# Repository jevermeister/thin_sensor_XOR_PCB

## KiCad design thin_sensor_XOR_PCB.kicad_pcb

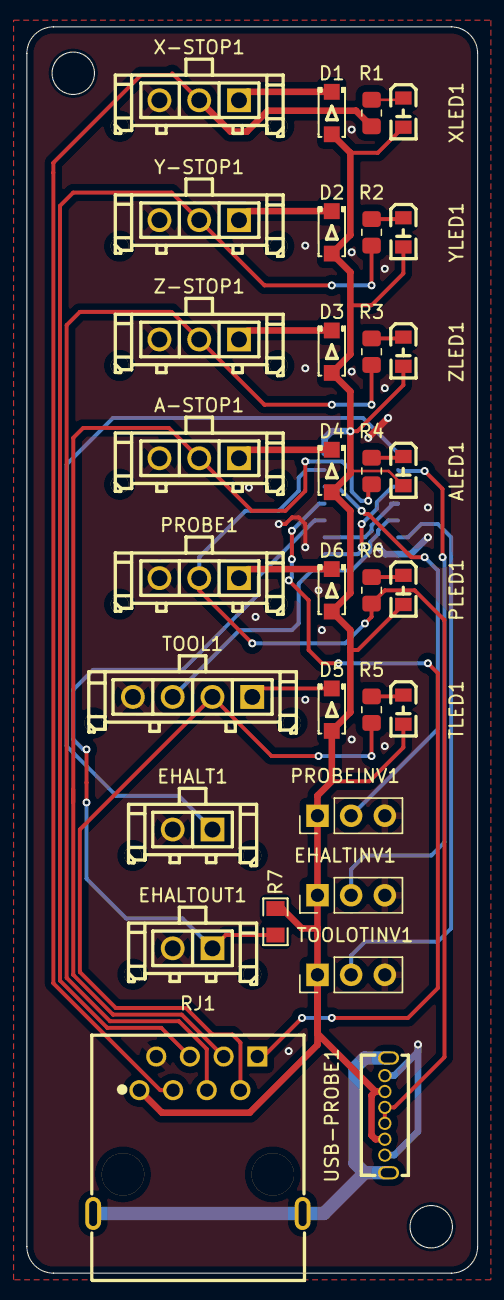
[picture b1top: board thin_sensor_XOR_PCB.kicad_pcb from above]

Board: 2 copper layers, 34.0 x 94.0 mm, 33 parts (1 on the bottom side), 30 nets.

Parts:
A-STOP1: Molex Microfit 3.0 43650-0315; CONN-TH_436500315
ALED1: LED0805-RD_RED
D1, D2, D3, D4, D5, D6: DSS14; SOD-123FL_L2.8-W1.8-LS3.7-RD
EHALT1: Molex Microfit 3.0 436500215; CONN-TH_436500215
EHALTINV1: Header-Male-2.54_1x3; PinHeader_1x03_P2.54mm_Vertical
EHALTOUT1: Molex Microfit 3.0 436500215; CONN-TH_436500215
PLED1: LED0805-RD_RED
PROBE1: Molex Microfit 3.0 43650-0315; CONN-TH_436500315
PROBEINV1: Header-Male-2.54_1x3; PinHeader_1x03_P2.54mm_Vertical
R1, R2, R3, R4, R5, R6: 3.3K; R_0805_2012Metric_Pad1.20x1.40mm_HandSolder
R7: 33K; R0805
RJ1: KH-RJ45-58-8P8C; RJ45-TH_KH-RJ45-58-8P8C
TLED1: SZYY0603R; LED0805-RD_RED
TOOL1: Molex Microfit 3.0 43650-0415; CONN-TH_436500415
TOOLOTINV1: Header-Male-2.54_1x3; PinHeader_1x03_P2.54mm_Vertical
U1: CD4030BM96; SOIC-14_L8.7-W3.9-P1.27-LS6.0-BL
USB-PROBE1: KH-TYPE-C-L10-6P; USB-C-TH_KH-TYPE-C-L10-6P
X-STOP1: Molex Microfit 3.0 43650-0315; CONN-TH_436500315
XLED1: LED0805-RD_RED
Y-STOP1: Molex Microfit 3.0 43650-0315; CONN-TH_436500315
YLED1: SZYY0603B; LED0805-RD_RED
Z-STOP1: Molex Microfit 3.0 43650-0315; CONN-TH_436500315
ZLED1: LED0805-RD_RED

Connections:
Aend: A-STOP1.2, R4.1, RJ1.6
EhaltOut: EHALTOUT1.1, R7.2, U1.10 (L)
ExtEhalt: U1.3 (J), U1.8 (E)
ExtEhaltInput: EHALT1.1, U1.1 (A)
ExtEhaltInvert: EHALTINV1.2, U1.2 (B)
GND: A-STOP1.3, EHALT1.2, EHALTINV1.3, EHALTOUT1.2, PROBE1.3, PROBEINV1.3, RJ1.2, TOOL1.4, TOOLOTINV1.3, U1.7 (VSS), USB-PROBE1.A12 (GND), USB-PROBE1.B12 (GND), X-STOP1.3, Y-STOP1.3, Z-STOP1.3
unnamed: ALED1.1 (C), R4.2
unnamed: D1.1 (K), X-STOP1.1
unnamed: D2.1 (K), Y-STOP1.1
unnamed: D3.1 (K), Z-STOP1.1
unnamed: A-STOP1.1, D4.1 (K)
unnamed: D5.1 (K), TOOL1.1
unnamed: D6.1 (K), PROBE1.1
unnamed: PLED1.1 (C), R6.2
unnamed: R5.2, TLED1.1 (C)
unnamed: R1.2, XLED1.1 (C)
unnamed: R2.2, YLED1.1 (C)
unnamed: R3.2, ZLED1.1 (C)
Probe: RJ1.8, U1.11 (M)
ProbeInput: PROBE1.2, R6.1, U1.13 (H), USB-PROBE1.A5 (CC1), USB-PROBE1.B5 (CC2)
ProbeInvert: PROBEINV1.2, U1.12 (G)
Shield: RJ1.9, RJ1.10, USB-PROBE1.1 (SHELL), USB-PROBE1.2 (SHELL)
Tool: R5.1, RJ1.7, TOOL1.2
ToolOverTravelInvert: TOOLOTINV1.2, U1.6 (D)
ToolOvertravel: U1.4 (K), U1.9 (F)
ToolOvertravelInput: TOOL1.3, U1.5 (C)
VCC: ALED1.2 (A), D1.2 (A), D2.2 (A), D3.2 (A), D4.2 (A), D5.2 (A), D6.2 (A), EHALTINV1.1, PLED1.2 (A), PROBEINV1.1, R7.1, RJ1.1, TLED1.2 (A), TOOLOTINV1.1, U1.14 (VDD), USB-PROBE1.A9 (VBUS), USB-PROBE1.B9 (VBUS), XLED1.2 (A), YLED1.2 (A), ZLED1.2 (A)
Xend: R1.1, RJ1.3, X-STOP1.2
Yend: R2.1, RJ1.4, Y-STOP1.2
Zend: R3.1, RJ1.5, Z-STOP1.2

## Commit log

2024-08-16 Initial commit of the EASYEDA conversion
2024-08-17 Removed jumpers and XOR combinations I don't need
2024-08-17 Added footprints, models etc
2024-08-18 Added / corrected 3D models
2024-08-18 Removed the correct RJ45 port this time
2024-10-05 Finished schematic and layout
2024-11-10 Added 3d models and recent version
2024-11-10 Added last step files
